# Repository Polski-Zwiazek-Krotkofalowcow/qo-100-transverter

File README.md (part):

# qo-100-transverter

*[Wersja polska / Polish version](README_PL.md)*

## What it's about
- source-available, hardware and software project of a transverter for the [QO-100](https://amsat-uk.org/satellites/geo/eshail-2/) satellite. The outdoor version takes 1.5 days to assemble starting from bare PCB, bag of parts, and patience.
- complete up and down-converter below 199,99 € : [see the BOM](hw-trv/BOM.md)
- in-fab assembly automation in progress

## Equipment and skills required
- knack for SMD soldering with stencil and solder paste
- patience for by-hand component placement
- 10x10 cm heat plate and ability to control the temperature profile
- multimeter
- set of fixed attenuators, a variable one and patch cables
- VNA+SA and a signal generator up to 3GHz minimum
- Pluto-like SDR to receive, measure, and generate signals during tests and adjustments
- RF power meter
- 30V 5A lab power supply with over-current protection
- ST-link programmer
- patience for drilling holes in aluminum enclosure
- patience for tapping 3 mm holes
- RF personal protective equipment rated to attenuate 2.4 GHz frequencies

## Features
- QO-100 narrow-band transponder SSB, CW, and Data operation with an HF-VHF transceiver
- ±0.25 ppm reference oscillator stability
- 6W of 2.4GHz output power
- 10m, 6m, 4m, 2m, 70cm bands supported, 5W input power maximum
- 738MHz filtered, receive output for signal supervision
- 25MHz reference oscillator for LNB: injected into the LNB feeder or the shared output
- PTT-over-coax supported
- splash-proof outdoor version

## Block diagram

## Operation

### Prerequisites

- 28V DC power supply offering 1.1A (31W), or
- 13.8V DC at 3.5A and using the Companion Box for voltage boost
- 60cm dish antenna suggested with 5W ERP according to AMSAT guidelines
- standard universal LNB (13/18V), 500mA fused
- standard PTT ground-to-transmit, or
- PTT-over-coax by transceiver or using the Companion Box to mix PTT and RF
- operation from 13.8V (1.1A) directly is possible with lower output power (2W max). Adequate linearity is not guaranteed.

### Basic procedures

1. Configure IF (Intermediate Frequency) corresponding to your transceiver setup using the three-position slide switch to select one of eight possible IF base frequencies.
2. IF can be updated on-the-fly, the change is indicated by a flashing green LED.
3. Connect DC power and PTT signal.
4. Switch on RX pre-amp in your transceiver.
5. Check the position of the received QO-100 mid beacon, adjust it to fall into the middle of the band using REF ADJ control with a small flat-head screwdriver.
6. Set your transceiver output power to 3–5W and adjust TX ATT control so that your signal is at the mid-beacon level. Lower power with a higher TX ATT setting is advised to minimize heat dissipation inside the transverter.

## Schematics

- [v1.1 schematics (current)](hw-trv/sch_v1.1.pdf) — extra input for 25MHz, idea from Zbig SP3NYF
- [v1.0 schematics](hw-trv/sch_v1.0.pdf) — cheap mini SAW filters + minor enhancements
- [v0.2 schematics](https://github.com/sq5nry/qo-100-transverter/blob/77cc88346982ab3cb6913bec3531f18df363a01a/hw-trv/sch_v0.2.pdf) — release presented at [Ham Radio Friedrichshafen 2026](https://www.hamradio-friedrichshafen.com/trade-show-program/exhibitors/exhibitor?id=107515806) in [PZK](https://www.pzk.org.pl/) (Polish Amateur Radio Union) tent

### PCB manufacturing

The production file set for ordering the v1.1 PCB at [JLCPCB](https://jlcpcb.com/) is available as [qo100_v1.1_jlc_pcb.7z](hw-trv/qo100_v1.1_jlc_pcb.7z).

## Assembly

### Preparation

Gather all parts from the [BOM](hw-trv/BOM.md) and arrange them on your workbench before starting.
Verify IC orientation markings and keep ESD-sensitive parts (ICs, MOSFETs) in their packaging
until placement.

### Solder paste application

Apply solder paste through the PCB stencil. Two paste options have been tested:

- **Sn63Pb37** (183°C eutectic, e.g. Mechanic XG-50) — recommended; standard SnPb profile,
  widely available, easy to work with.
- **Sn42Bi58** (~138°C eutectic, e.g. ChipQuik SMD291 or Mechanic UV50) — low-melting-point
  alternative; useful if heat-sensitive components are a concern, but requires careful handling
  as bismuth alloys are more brittle and less compatible with lead-containing component finishes.

Clamp the stencil firmly over the PCB, apply paste with a squeegee in a single smooth stroke,
and lift the stencil straight up to avoid smearing. Inspect paste deposits under magnification
before placing components.

### Component placement

Place all SMD components onto the paste deposits. Work from smallest to largest — passives first,
then ICs. Pay close attention to pin-1 orientation on all ICs and polarised components.
QFN packages require careful centring over their pads; the paste surface tension will self-align
them slightly during reflow.

### Reflow

Place the populated PCB on the heat plate. Follow a standard **SnPb reflow profile**:

| Zone | Temperature | Duration |
|------|------------|---------|
| Preheat | 100–150°C | ~60 s |
| Soak | 150–180°C | 60–90 s |
| Reflow (above liquidus) | 183–215°C peak | 30–45 s |
| Cooldown | ramp down | natural |

Use hot air to assist reflow around QFN packages and larger thermal-mass parts (PA, DC-DC
converter). Watch for bridging on fine-pitch ICs.
Best option is using a dedicated reflow oven. Otherwise you'll obtain good results with a makeshift greenhouse made from transparent plastics.

### Inspection and rework

After reflow and cooldown, inspect all joints under magnification:

- Remove solder bridges with braid or a fine soldering iron tip.
- Add solder to any under-filled joints, particularly on exposed thermal pads of QFN/PQFN
  packages — use a soldering iron with flux through the heat-via holes on the bottom side.
- The bottom-side thermal vias do not need to be flush; they will be covered by thermal pads
  connecting to the heat spreader or enclosure floor.

### Through-hole parts

Solder the 5W power resistor by hand after SMD reflow. Mount the TCVCXO with polyester
tape and foam fitting as described in the enclosure assembly notes.

### EMI shields

The PCB has footprints for SMD metal EMI shields over sensitive sections. Mounting the shield over the IF Unit is important for stability. Shielding the switched-mode power supply section and TCXO is recommended but not critical.
I haven't noticed any adverse effects with no EMI shields at all, especially with metal enclosure and EMI absorber mounted.

### EMI absorber

Most of enclosure types require absorption foams in PA area to help suppress self-oscillations and minimize parasitic coupling between stages. The amplifier may start self-oscillations at a frequency between 2.2-2.5GHz with full power without the absorber. \
See gallery section for a poor's-man approach.

### PCB cleaning

Wash the assembled PCB thoroughly with isopropanol to remove all flux residues before
proceeding. Flux contamination on the board surface can significantly affect 2.4GHz circuit
behaviour — altering tuning, increasing losses, and making RF adjustments unreliable.
Allow the board to dry completely before applying power.

### Power-up and initial checks

Connect power and PTT cables. Supply 28V with the current limit set to 50mA. Measure the
following test points and verify voltages before proceeding:

1. Check 13V and 5V test points first.
2. If those are correct, verify: 3V (analog), 3V (digital), 3.3V (reference oscillator),
   3V (MCU), 9V, and 1.8V.

If any rail is missing or out of range, do not proceed — investigate before applying full power.

### Firmware

Flash the firmware using **STM32CubeProgrammer** via the ST-LINK interface and the SWD ISP
header. A firmware release binary is provided; to build from source use **STM32CubeIDE**.

After programming, the **PLL LOCK** indicator should illuminate. If it does not, check the
25MHz reference oscillator signal.

### PA bias adjustment

Set the quiescent drain current (Idq) for the 2.4GHz PA stages:

- 1st stage: **15mA**
- 2nd stage: **75mA**

Before adjusting, raise the lab supply's overload protection (current limit) to about
**250mA** so it does not trip during bias trimming.

To measure Idq, cut the respective drain supply PCB trace and insert an ammeter in series or just calculate current delta on the lab supply.
Adjust the bias trimmer for each stage until the target Idq is reached, then bridge the cut
with solder.
Adjust the position of C87 in the PA output circuit for highest stage gain.

### PA gain and output matching

Measure the PA gain and adjust the position of C88 to obtain **28–30dB** gain — slide C88 along the output line toward the thicker section. If that alone does not maximise gain, add 0.8pF in parallel with C88. Do not mount the low-pass filter (LPF) elements yet — bridge the LPF inductor footprint with a strip of
copper foil instead, so the PA output can be measured without the potentially mismatched filter.

Once the gain is set, mount the LPF inductor and adjust it for a maximum insertion loss of
**1dB at 2.4GHz**.

Set the overload (overcurrent) protection threshold to **1.1A**.

Connect an RF power meter to the 2.4GHz TX output socket and adjust the TX path for **6W**
output across your expected input power range (1–5W).

> **⚠️ Warning:** do not increase input power in an attempt to reach 6W until PA gain is at least 28dB. PA chip will overheat and operate non-linearly. I bricked one PA after overloading its input with just 17dBm.

> **⚠️ Warning:** do not drive the PA past **9..12W** output — exceeding this limit pushes the
> stage into non-linear operation, causing spectral splatter and interference to other users.

> **⚠️ Note:** the PA chip tolerates antenna mismatch well — SWR up to 10:1 on the 2.4GHz
> TX port will not damage it. However, operating with no load connected may cause
> self-oscillation in the 2.2–2.5GHz range; the on-board 1.5A resettable fuse will limit
> the resulting current in that event.

## Circuit description

### Transmit path

The transceiver signal (up to 5W / +37dBm) passes through a variable 35–42dB attenuator,
reducing it to approximately −8dBm at the mixer input. A diode protection limiter with a
clipping level starting softly at +4dBm guards the mixer — this is to limit damage in case you connect 100W for a longer time. Note that sustained high-power overshoots may still damage the PA by exceeding its maximum input level even if the mixer itself survives. \
The signal enters a balanced Gilbert-cell mixer (RFFC2071). The mixer's wideband 4:1 output transformer provides differential symmetry that helps cancel LO leakage, minimising it before the signal
 reaches the downstream filter. Although slightly more expensive than a narrowband balun
chip, the wideband transformer's superior symmetry keeps LO leakage below −50dBc relative
to the upper sideband with only two mini SAW filters — most critically on the 29MHz band, where
LO leakage lands closest to occupied spectrum. The TX mixer on 10m is intentionally operated at a reduced  current, which directly decreases LO leakage at its output. \
The output is filtered by two 2.4GHz bandpass filters to further suppress residual LO leakage as well as the image. The driver stage amplifies the signal to +12dBm, followed by a 29dB LDMOS power amplifier — whose input is matched to 50Ω using a short high-impedance transmission line — and a low-pass filter, delivering +38dBm (6W) to
the TX output socket. \
1dB and 3dB fixed attenuation pads improve impedance matching, distribute gain, and improve amplifier stability.\
Image attenuation is better than 60dB on 10m.
Total conversion gain is 2–9dB; about 0.8–4W from the transceiver will produce 6W output.

### Receive path

Both the LNB supply voltage and the 25MHz reference signal (along with its harmonics up to 125MHz) are injected via a bias-T, which must provide sufficient RF isolation across the full 25–738MHz range where these signals share the same junction. The reference signal is low-pass filtered to 125MHz before injection. \
The received 738MHz IF from the LNB passes through a high-pass filter (so as not to hammer the input SAW filters with the reference oscillator) and two cascaded SAW filters centred around 738MHz. Then follows optional splitter to tap IF to the external RX AUX socket. Release v0.2 uses resistive splitter but it's advised to use minimum-loss option as in v0.3-sh. If you don't need the RX AUX output, do not mount the splitter parts.\
From the mixer output the signal passes through a PIN diode switch to the shared TRX socket. The switch's bias-T is built from three inductors in series, chosen to present at least 1kΩ of reactance at
every supported IF band. \
The input attenuator is always present on the RX path — enable the RX preamplifier in your
transceiver to compensate. The receive path does not add amplification (to keep the cost low) and relies on typical LNB signal levels so as not to degrade the SNR with noise from the RX chain. \
On 70cm IF the strongest signals come at S9 level with RX preamp on, mid-beacon is S7.

### Control

The STM32L0 microcontroller configures the RFFC2071 PLL for the RX and TX frequencies corresponding to the IF band selected by the DIP switch. In addition, mixer bias currents ate also configurd per band. On PTT transitions, the logic switches between the TX and RX PLL register banks in the RFFC2071. The PTT signal is a logical OR from the physical PTT line and the coax (PTT-over-coax).

### Indicators

The blue LED indicates that the PLL synthesizer is locked — the MCU has configured the PLL, the 25MHz reference is running, and the LO frequency is being generated. Mixer bias currents are configured according to IF band.

The green LED blinks in RX mode and is lit continuously in TX mode. On startup and on IF band change, it blinks once per IF position number (1–8).

## Jumper configuration

### Jumper reference

| Jumper | Name | Default | Function |
|--------|------|---------|----------|
| JP1 | AUX SEL | Reference | Selects what the RX/REF (AUX) socket outputs: **Reference** (25MHz) or **RX** (738MHz) |
| JP2 | RX SPLIT | no-split | Part of RX split — change together with JP4. Change position only if you want RX in AUX socket. |
| JP4 | RX SPLIT | no-split | Part of RX split — change together with JP2. Change position only if you want RX in AUX socket. |
| JP5 | OVEN | disconnected | Reserved for OCXO option; disabled in v0.2 |
| JP6 | REF ROUTE | AUX path | Routes the 25MHz reference toward the AUX socket (default) or toward the LNB feeder (also check JP7) |
| JP7 | REF TO LNB | open | Solder to mix the 25MHz reference signal into the LNB feeder coax. This jumper enhances signal integrity when the REF signal isn't routed to the LNB feeder. "Open" when you don't want to mix the REF with the LNB feeder, "Connected" to inject the REF into the LNB feeder. |
| JP8 | REF SEL | ext ref | Selects the source of the 25MHz reference signal: the **internal TCXO** or an **external reference** fed to the REF_IN socket. |
| JP9 | REF_IN TERM | open | Connects the internal 50Ω termination to REF_IN. "Open" leaves REF_IN unterminated, "Connected" (solder) terminates it with 50Ω. |

### Typical usage scenarios

**1. RX/REF (AUX) socket outputs 25MHz reference** *(default — no changes needed)*

Use this to supply 25MHz reference to an external device via the AUX socket.

| JP1 | JP2 | JP4 | JP6 | JP7 |
|-----|-----|-----|-----|-----|
| default (Reference) | default | default | default (AUX path) | open |

---

**2. 25MHz reference injected into LNB feeder cable**

Use this when the LNB is fed its reference via the coax (no separate reference cable needed).

| JP1 | JP2 | JP4 | JP6 | JP7 |
|-----|-----|-----|-----|-----|
| default | default | default | **change (LNB path)** | **solder** |

---

**3. RX signal (738MHz) on AUX socket**

Use this to route the received downconverted signal to an external SDR or receiver via the AUX socket.

| JP1 | JP2 | JP4 | JP6 | JP7 |
|-----|-----|-----|-----|-----|
| **change (RX)** | **change** | **change** | default | open |

---

**4. Reference injected into LNB feeder + RX signal on AUX socket**

Combines use cases 2 and 3: LNB gets its reference via coax, AUX socket carries the RX signal.

| JP1 | JP2 | JP4 | JP6 | JP7 |
|-----|-----|-----|-----|-----|
| **change (RX)** | **change** | **change** | **change (LNB path)** | **solder** |

---

## Gallery

<table>
<tr>
<td align="center"><br><em>Click the image to watch the video.</em></td>
<td align="center"><br><em>Infrared video of the PCB during PA test — passive cooling via aluminum enclosure. Click to watch.</em></td>
</tr>
</table>

<table>
<tr>
<td align="center"><br><em>Output power — click to watch. 40dB/50W att. + 20dB SMA att (39.5+19,5=59dB at 2.4GHz)</em></td>
<td align="center"><br><em>Power measurements — click to watch. Heat-pipe directly at PA.</em></td>
</tr>
</table>

### v1.0 bare board

<table>
<tr>
<td></td>
<td></td>
</tr>
</table>

### Finished units

<table>
<tr>
<td><br><em>cabinet, outdoor classic, outdoor mini, bare bone</em></td>
<td><br><em>cabinet version</em></td>
</tr>
<tr>
<td><br><em>outdoor mini</em></td>
<td><br><em>Companion Box</em></td>
</tr>
<tr>
<td><br><em>cabinet version, back plate</em></td>
<td><br><em>cabinet mini</em></td>
</tr>
</table>

### Enclosure internals

<table>
<tr>
<td><br><em>cabinet version</em></td>
<td><br><em>outdoor classic</em></td>
</tr>
<tr>
<td><br><em>cabinet version</em></td>
<td><br><em>cabinet version</em></td>
</tr>
<tr>
<td><br><em>Companion Box proof-of-concept</em></td>
<td><br><em>outdoor mini</em></td>
</tr>
</table>

### PCB assembly

<table>
<tr>
<td></td>
<td></td>
<td></td>
</tr>
<tr>
<td></td>
<td></td>
<td></td>
</tr>
<tr>
<td></td>
<td></td>
<td></td>
</tr>
<tr>
<td></td>
<td></td>
<td></td>
</tr>
<tr>
<td></td>
<td></td>
<td></td>
</tr>
</table>

### PCB details

<table>
<tr>
<td><br><em>2.8GHz low-pass filter</em></td>
<td></td>
</tr>
<tr>
<td></td>
<td></td>
</tr>
<tr>
<td><br><em>replacing IF chip</em></td>
<td></td>
</tr>
</table>

### EMI absorbers

<table>
<tr>
<td></td>
<td></td>
</tr>
<tr>
<td></td>
<td></td>
</tr>
</table>

### Development and testing

<table>
<tr>
<td></td>
<td></td>
</tr>
<tr>
<td></td>
<td></td>
</tr>
<tr>
<td></td>
<td></td>
</tr>
<tr>
<td></td>
<td></td>
</tr>
<tr>
<td></td>
<td><br><em>a cheap C88 (ordinary ceramic instead of ATC porcelain one)</em></td>
</tr>
</table>

### Measurements

<table>
<tr>
<td></td>
<td></td>
</tr>
</table>

## Measurements - TX & RX paths

### TX mixer-to-driver-out, LDMOS gain

<table>
<tr>
<td></td>
<td></td>
</tr>
</table>

### LO, upper sideband, image, and 2nd harmonic levels

<table>
<tr>
<td></td>
<td></td>
</tr>
<tr>
<td></td>
<td></td>
</tr>
</table>

### TRX port

<table>
<tr>
<td align="center"><br><em>TRX port on TX, s11</em></td>
<td align="center"><br><em>TRX port on RX, s11</em></td>
</tr>
</table>

> **⚠️ Note:** TX SWR on 23cm is high. Only RX has been tested and confirmed on this band. Proper TX 23cm testing is in progress — it may work with ALC-limited power from your transceiver.

### RF filtering

*two 739MHz filters cascaded incl. balun loss*

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
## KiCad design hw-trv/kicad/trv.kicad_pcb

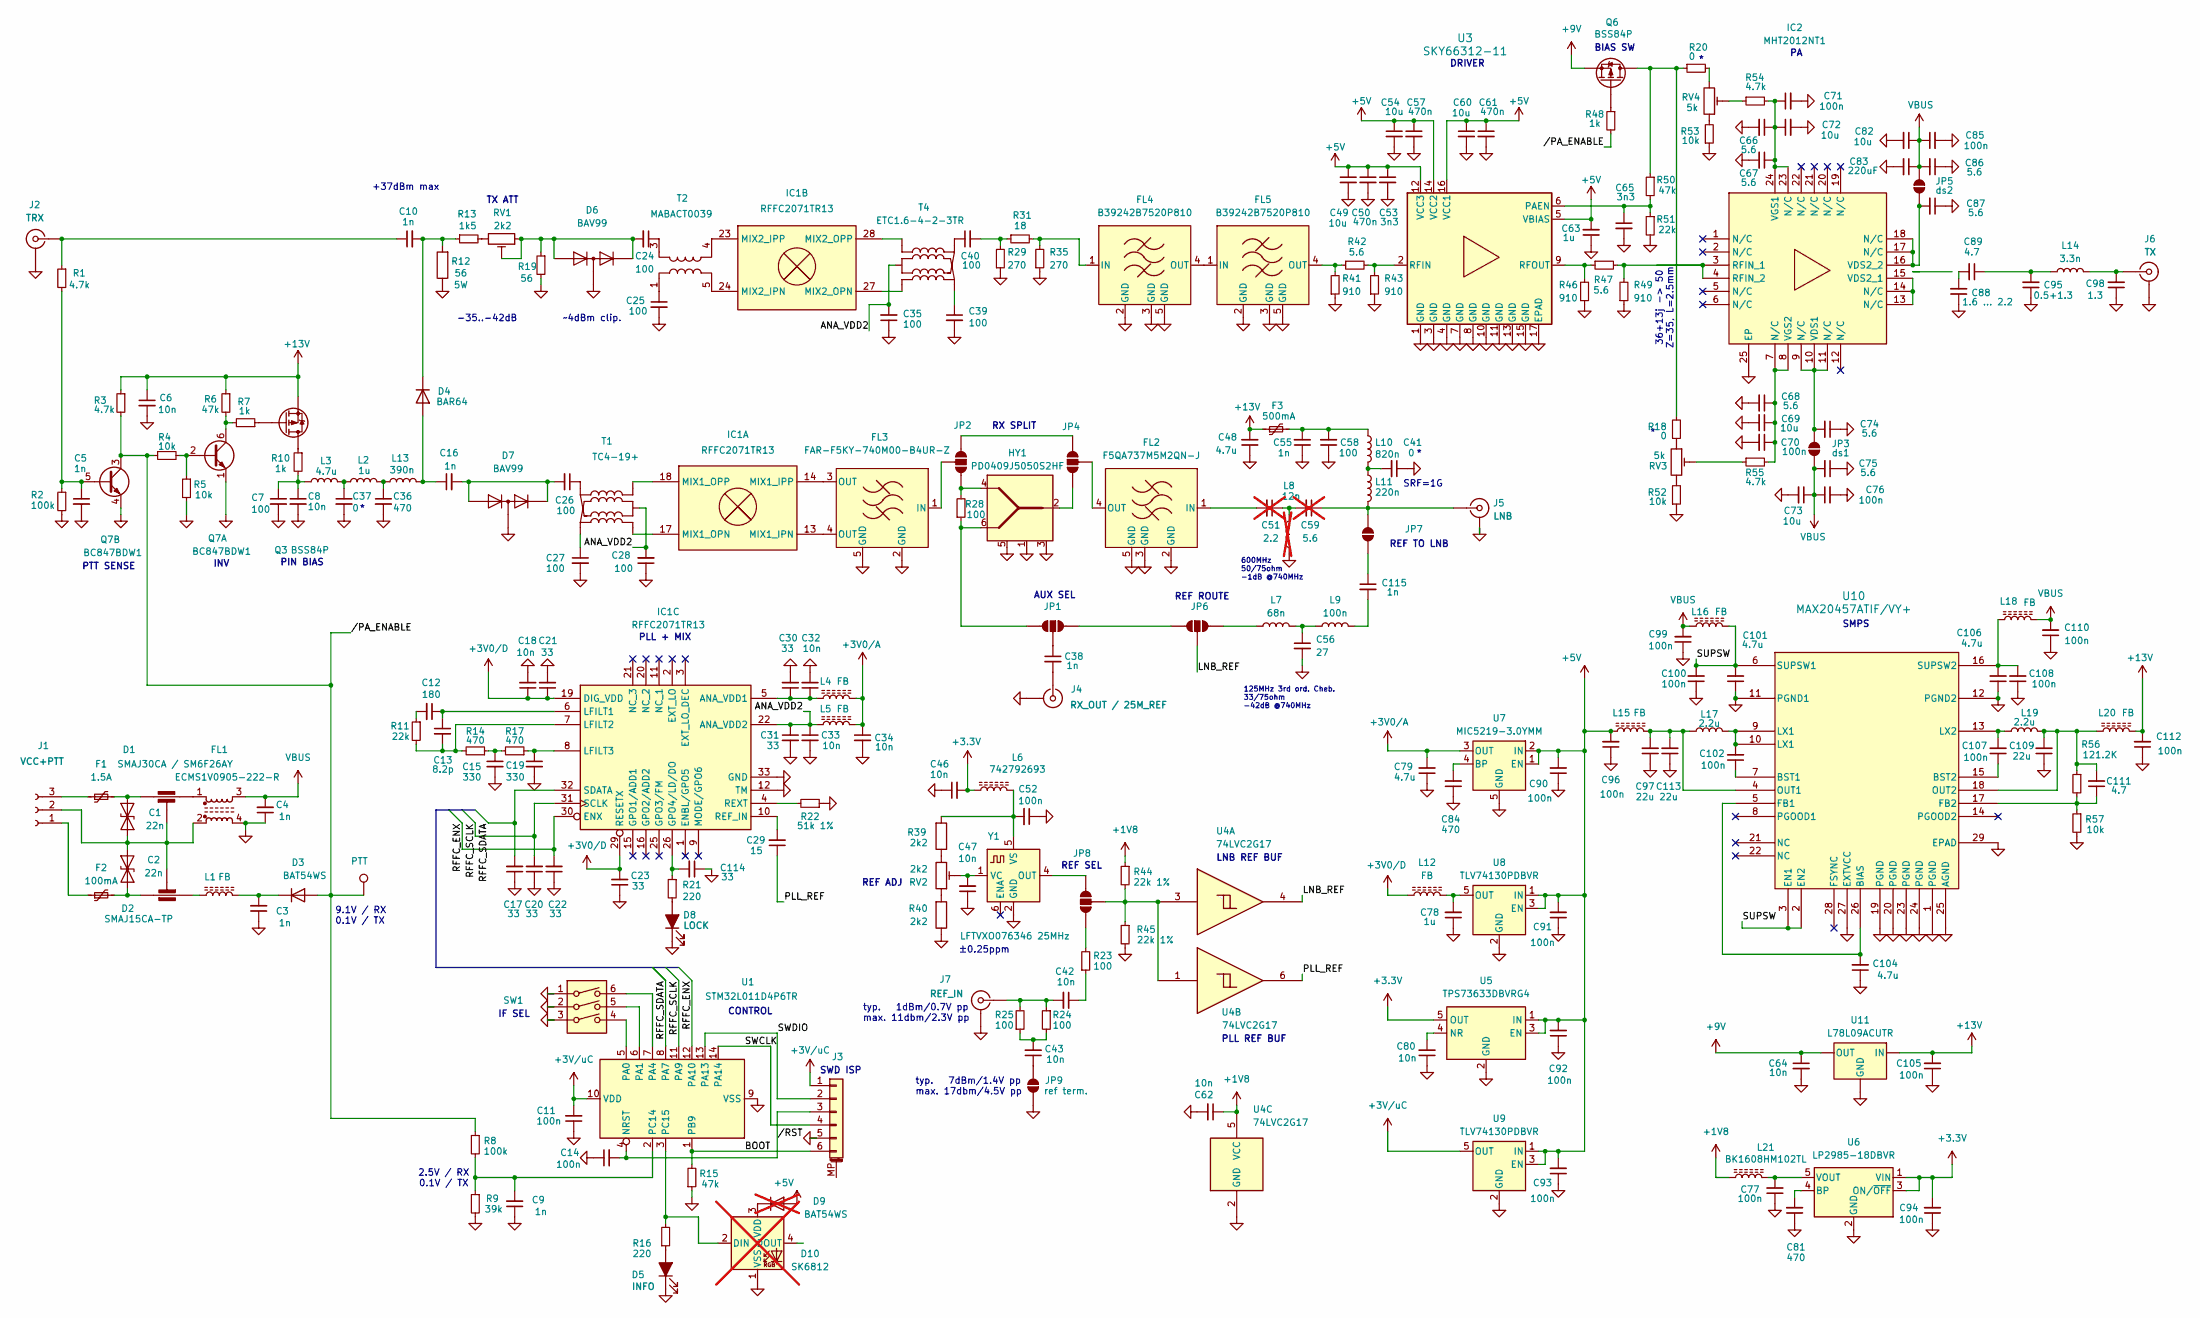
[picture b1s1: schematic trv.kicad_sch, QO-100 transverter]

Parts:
C1: 22n; Filter_Mini-Circuits_FV1206; Voltage 100V
C2: 22n; Filter_Mini-Circuits_FV1206; Voltage 50V
C3, C4, C5, C9, C16, C38, C55, C115: 1n; C_0603_1608Metric_Pad1.08x0.95mm_HandSolder; Voltage 35V
C6, C8, C18, C32, C33, C34, C46, C47, C62, C64, C80: 10n; C_0603_1608Metric_Pad1.08x0.95mm_HandSolder; Voltage 16V
C7, C58: 100; C_0603_1608Metric_Pad1.08x0.95mm_HandSolder; Voltage 35V
C10: 1n; C_0603_1608Metric_Pad1.08x0.95mm_HandSolder; Voltage 100V
C11, C14, C52, C77, C90, C91, C92, C93, C94: 100n; C_0603_1608Metric_Pad1.08x0.95mm_HandSolder; Voltage 16V
C12: 180; C_0603_1608Metric_Pad1.08x0.95mm_HandSolder; Voltage 16V
C13: 8.2p; C_0603_1608Metric_Pad1.08x0.95mm_HandSolder; Voltage 16V
C15, C19: 330; C_0603_1608Metric_Pad1.08x0.95mm_HandSolder; Voltage 16V
C17, C20, C21, C22, C23, C30, C31, C114: 33; C_0603_1608Metric_Pad1.08x0.95mm_HandSolder; Voltage 16V
C24, C25, C26, C27, C28, C35, C39, C40: 100; C_0603_1608Metric_Pad1.08x0.95mm_HandSolder; Voltage 16V
C29: 15; C_0603_1608Metric_Pad1.08x0.95mm_HandSolder; Voltage 16V
C36: 470; C_0603_1608Metric_Pad1.08x0.95mm_HandSolder; Voltage 35V
C37, C41: 0; C_0603_1608Metric_Pad1.08x0.95mm_HandSolder; Voltage 35V
C42, C43: 10n; C_0603_1608Metric_Pad1.08x0.95mm_HandSolder; Voltage 35V
C48: 4.7u; C_1206_3216Metric; Voltage 25V
C49, C54, C60: 10u; C_1210_3225Metric; Voltage 16V
C50, C57, C61: 470n; C_0603_1608Metric_Pad1.08x0.95mm_HandSolder; Voltage 16V
C51: 2.2; C_0603_1608Metric_Pad1.08x0.95mm_HandSolder; Voltage 35V; not fitted
C53, C65: 3n3; C_0603_1608Metric_Pad1.08x0.95mm_HandSolder; Voltage 16V
C56: 27; C_0603_1608Metric_Pad1.08x0.95mm_HandSolder; Voltage 35V
C59: 5.6; C_0603_1608Metric_Pad1.08x0.95mm_HandSolder; Voltage 35V; not fitted
C63, C78: 1u; C_0603_1608Metric_Pad1.08x0.95mm_HandSolder; Voltage 16V
C66, C67, C68, C74, C75, C86, C87: 5.6; L_0805_2012Metric; Voltage 250V
C69, C72, C73, C82: 10u; C_1210_3225Metric; Voltage 50V
C70, C71, C76, C85: 100n; C_1210_3225Metric; Voltage 100V
C79: 4.7u; CP_EIA-3528-21_Kemet-B_HandSolder; Voltage 10V
C81, C84: 470; C_0603_1608Metric_Pad1.08x0.95mm_HandSolder; Voltage 16V
C83: 220uF; CP_Elec_6.3x5.8; Voltage 35V
C88: 1.6 ... 2.2; C_0805_2012Metric; Voltage 250V
C89: 4.7; C_0805_2012Metric_Pad1.18x1.45mm_HandSolder; Voltage 250V
C95: 0.5+1.3; C_0805_2012Metric; Voltage 250V
C96, C99, C100, C108, C110: 100n; C_1206_3216Metric; Voltage 35V
C97, C113: 22u; C_1206_3216Metric_Pad1.33x1.80mm_HandSolder; Voltage 10V
C98: 1.3; C_0805_2012Metric; Voltage 250V
C101, C106: 4.7u; C_1206_3216Metric; Voltage 35V
C102, C107: 100n; C_0603_1608Metric; Voltage 50V
C104: 4.7u; C_0603_1608Metric_Pad1.08x0.95mm_HandSolder; Voltage 16V
C105: 100n; C_0603_1608Metric_Pad1.08x0.95mm_HandSolder; Voltage 50V
C109: 22u; C_1206_3216Metric_Pad1.33x1.80mm_HandSolder; Voltage 25V
C111: 4.7; C_0603_1608Metric_Pad1.08x0.95mm_HandSolder; Voltage 35V
C112: 100n; C_1206_3216Metric_Pad1.33x1.80mm_HandSolder; Voltage 35V
D1: SMAJ30CA / SM6F26AY; D_SMA
D2: SMAJ15CA-TP; D_SMA
D3: BAT54WS; D_SOD-323F
D4: BAR64; D_SOD-523
D5: INFO; LED_0805_2012Metric_Pad1.15x1.40mm_HandSolder
D6, D7: BAV99; SOT-23-3
D8: LOCK; LED_0805_2012Metric_Pad1.15x1.40mm_HandSolder
D9: BAT54WS; D_SOD-323F; not fitted
D10: SK6812; LED_SK6812_PLCC4_5.0x5.0mm_P3.2mm; not fitted
F1: 1.5A; Fuse_2920_7451Metric_Pad2.10x5.45mm_HandSolder
F2: 100mA; Fuse_1210_3225Metric_Pad1.42x2.65mm_HandSolder
F3: 500mA; Fuse_1206_3216Metric_Pad1.42x1.75mm_HandSolder
FL1: ECMS1V0905-222-R; L_CommonModeChoke_TDK_ACM7060
FL2: F5QA737M5M2QN-J; SMD5_SAW-B7520_QUA
FL3: FAR-F5KY-740M00-B4UR-Z; FAR-F5KY
FL4, FL5: B39242B7520P810; SMD5_SAW-B7520_QUA
HY1: PD0409J5050S2HF; Manufacturer_Part_Number PD0409J5050S2HF; Mouser Part Number 620-PD0409J5050S2HF
IC1: RFFC2071TR13; Manufacturer_Part_Number RFFC2071TR13; Mouser Part Number 772-RFFC2071
IC2: MHT2012NT1; Mouser Part Number 771-MHT2012NT1
J1: VCC+PTT; 874370363
J2: TRX; SMA_Amphenol_132289_EdgeMount
J3: SWD ISP; PinHeader_2x03_P2.54mm_Vertical_SMD
J4: RX_OUT / 25M_REF; SMA_Amphenol_132289_EdgeMount
J5: LNB; 222131
J6: TX; SMA_Wurth_60312102114405_Vertical
J7: REF_IN; SMA_Amphenol_132289_EdgeMount
JP1, JP2, JP4, JP6, JP8: SolderJumper_3_Open; SolderJumper-3_P1.3mm_Bridged12_RoundedPad1.0x1.5mm_NumberL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
JP3: ds1
JP5: ds2
JP7: SolderJumper_2_Open; SolderJumper-2_P1.3mm_Open_RoundedPad1.0x1.5mm
JP9: ref term.; SolderJumper-2_P1.3mm_Open_RoundedPad1.0x1.5mm
L1, L15, L16, L18, L20: FB; L_1812_4532Metric_Pad1.30x3.40mm_HandSolder
L2: 1u; L_1008_2520Metric_Pad1.43x2.20mm_HandSolder
L3: 4.7u; L_0805_2012Metric_Pad1.05x1.20mm_HandSolder
L4, L5, L12: FB; L_0603_1608Metric_Pad1.05x0.95mm_HandSolder
L6: 742792693; L_0603_1608Metric_Pad1.05x0.95mm_HandSolder
L7: 68n; L_0805_2012Metric_Pad1.05x1.20mm_HandSolder
L8: 12n; L_0603_1608Metric_Pad1.05x0.95mm_HandSolder; not fitted
L9: 100n; L_0805_2012Metric_Pad1.05x1.20mm_HandSolder
L10: 820n; L_1008_2520Metric_Pad1.43x2.20mm_HandSolder
L11: 220n; L_0603_1608Metric_Pad1.05x0.95mm_HandSolder
L13: 390n; L_Cenker_CKCS252012
L14: 3.3n; L_0805_2012Metric_Pad1.05x1.20mm_HandSolder
L17, L19: 2.2u; INDPM7168X300N
L21: BK1608HM102TL; L_0603_1608Metric_Pad1.05x0.95mm_HandSolder
PTT1: PTT; TestPoint_Pad_D1.5mm
Q3, Q6: BSS84P; SOT-23
Q7: BC847BDW1; SOT-363_SC-70-6
R1, R3, R54, R55: 4.7k; R_0603_1608Metric_Pad0.98x0.95mm_HandSolder
R2, R8: 100k; R_0603_1608Metric_Pad0.98x0.95mm_HandSolder
R4, R5, R52, R53, R57: 10k; R_0603_1608Metric_Pad0.98x0.95mm_HandSolder
R6, R15, R50: 47k; R_0603_1608Metric_Pad0.98x0.95mm_HandSolder
R7, R10, R48: 1k; R_0603_1608Metric_Pad0.98x0.95mm_HandSolder
R9: 39k; R_0603_1608Metric_Pad0.98x0.95mm_HandSolder
R11, R51: 22k; R_0603_1608Metric_Pad0.98x0.95mm_HandSolder
R12: 56; RES_3550_TEC
R13: 1k5; R_0603_1608Metric_Pad0.98x0.95mm_HandSolder
R14, R17: 470; R_0603_1608Metric_Pad0.98x0.95mm_HandSolder
R16, R21: 220; R_0603_1608Metric_Pad0.98x0.95mm_HandSolder
R18, R20: 0; R_0603_1608Metric_Pad0.98x0.95mm_HandSolder
R19: 56; R_0603_1608Metric_Pad0.98x0.95mm_HandSolder
R22: 51k 1%; R_0603_1608Metric_Pad0.98x0.95mm_HandSolder
R23, R24, R25, R28: 100; R_0603_1608Metric_Pad0.98x0.95mm_HandSolder
R29, R35: 270; R_0603_1608Metric_Pad0.98x0.95mm_HandSolder
R31: 18; R_0603_1608Metric_Pad0.98x0.95mm_HandSolder
R39, R40: 2k2; R_0603_1608Metric_Pad0.98x0.95mm_HandSolder
R41, R43, R46, R49: 910; R_0603_1608Metric_Pad0.98x0.95mm_HandSolder
R42, R47: 5.6; R_0603_1608Metric_Pad0.98x0.95mm_HandSolder
R44, R45: 22k 1%; R_0805_2012Metric_Pad1.20x1.40mm_HandSolder
R56: 121.2K; R_0603_1608Metric_Pad0.98x0.95mm_HandSolder
RV1: 2k2; Potentiometer_Bourns_TC33X_Vertical
RV2: 2k2; Potentiometer_Bourns_3314J_Vertical
RV3, RV4: 5k; Potentiometer_Bourns_TC33X_Vertical
SW1: SW_DIP_x03; SW_DIP_SPSTx03_Slide_KingTek_DSHP03TJ_W5.25mm_P1.27mm_JPin
T1: TC4-19+; ETC1.6-4-2-3TR_MCM
T2: MABACT0039; MABACT0039_MCM
T4: ETC1.6-4-2-3TR; ETC1.6-4-2-3TR_MCM
U1: STM32L011D4P6TR; TSSOP-14_4.4x5mm_P0.65mm
U3: SKY66312-11; QFN16_5X5_SKY
U4: 74LVC2G17; Vishay_PowerPAK_SC70-6L_Dual
U5: TPS73633DBVRG4; SOT-23-5
U6: LP2985-18DBVR; SOT-23-5
U7: MIC5219-3.0YMM; MSOP-8_3x3mm_P0.65mm
U8, U9: TLV74130PDBVR; SOT-23-5
U10: MAX20457ATIF/VY+; 21-100130_MXM
U11: L78L09ACUTR; SOT-89-3
Y1: LFTVXO076346 25MHz; LFTVXO076346REEL_IQD-M

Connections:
+1V8: C62.1, L21.1, R44.1, U4.5 (VCC)
+3.3V: C46.2, C94.2, L6.1, U5.5 (OUT), U6.1 (VIN), U6.3 (ON/~OFF)
+3V0/A: C34.1, C79.2, L4.2, L5.2, U7.3 (OUT); also elsewhere on the board
+3V0/D: C18.1, C21.1, C23.2, IC1.19 (DIG_VDD), IC1.29 (RESETX), L12.1; also elsewhere on the board
+3V/uC: C11.2, J3.1, U1.10 (VDD), U9.5 (OUT)
+5V: C49.1, C50.1, C53.1, C54.1, C57.1, C60.1, C61.1, C63.2, C90.2, C91.2, C92.2, C93.2, C96.2, D9.2 (A), L15.1, U3.5 (VBIAS), U3.12 (VCC3), U3.14 (VCC2), U3.16 (VCC1), U5.1 (IN), U5.3 (EN), U7.1 (EN), U7.2 (IN), U8.1 (IN), U8.3 (EN), U9.1 (IN), U9.3 (EN); also elsewhere on the board
+9V: C64.1, Q6.2 (S), U11.1 (OUT); also elsewhere on the board
+13V: C6.1, C48.2, C105.2, C112.2, F3.1, L20.2, Q3.2 (S), R3.1, R6.1, U11.3 (IN); also elsewhere on the board
/ANA_VDD2: C28.2, C31.1, C33.1, C35.2, IC1.22 (ANA_VDD2), L5.1, T1.2, T4.2
/BOOT: J3.6, R15.2, U1.1 (PB9)
/LNB_REF: JP6.2 (C), U4.4
/PLL_REF: C29.1, U4.6
/RFFC_ENX: C22.2, IC1.30 (ENX), U1.12 (PA10)
/RFFC_SCLK: C20.2, IC1.31 (SCLK), U1.11 (PA9)
/RFFC_SDATA: C17.2, IC1.32 (SDATA), U1.8 (PA7)
/SUPSW: C100.2, C101.2, L16.2, U10.2 (EN2), U10.3 (EN1), U10.6 (SUPSW1)
/SWCLK: J3.4, U1.14 (PA14)
/SWDIO: J3.2, U1.13 (PA13)
//PA_ENABLE: D3.2 (A), PTT1.1, Q7.3 (C2), R3.2, R4.1, R8.1, R48.2; also elsewhere on the board
//RST: C14.2, J3.3, U1.4 (NRST)
GND: C3.1, C4.1, C5.2, C6.2, C7.2, C8.2, C9.1, C11.1, C14.1, C15.2, C17.1, C18.2, C19.2, C20.1, C21.2, C22.1, C23.1, C25.2, C27.2, C28.1, C30.2, C31.2, C32.2, C33.2, C34.2, C35.1, C36.2, C37.2, C39.2, C41.1, C46.1, C47.1, C48.1, C49.2, C50.2, C52.1, C53.2, C54.2, C55.1, C56.2, C57.2, C58.1, C60.2, C61.2, C62.2, C63.1, C64.2, C65.2, C66.2, C67.2, C68.2, C69.2, C70.2, C71.2, C72.2, C73.2, C74.1, C75.1, C76.2, C77.1, C78.1, C79.1, C80.1, C81.1, C82.2, C83.2, C84.1, C85.2, C86.1, C87.1, C88.1, C90.1, C91.1, C92.1, C93.1, C94.1, C95.1, C96.1, C97.1, C98.1, C99.1, C100.1, C101.1, C104.1, C105.1, C106.1, C108.1, C109.1, C110.1, C112.1, C113.1, C114.1, D5.1 (K), D6.3 (K), D7.3 (K), D8.1 (K), D10.1 (VSS), FL1.4, FL2.2 (GND), FL2.3 (GND), FL2.5 (GND), FL3.2 (GND), FL3.5 (GND), FL4.2 (GND), FL4.3 (GND), FL4.5 (GND), FL5.2 (GND), FL5.3 (GND), FL5.5 (GND), HY1.1, HY1.3, HY1.5, IC1.12 (TM), IC1.33 (GND), IC2.25 (EP), J2.2 (Ext), J3.5, J4.2 (Ext), J5.2 (Ext), J6.2 (Ext), J7.2 (Ext), JP9.2 (B), L8.1, Q7.1 (E1), Q7.4 (E2), R2.2, R5.2, R9.2, R12.1, R15.1, R19.2, R22.1, R29.1, R35.1, R40.1, R41.1, R43.1, R45.2, R46.1, R49.1, R51.2, R52.1, R53.1, R57.2, SW1.1, SW1.2, SW1.3, U1.9 (VSS), U3.1 (GND), U3.3 (GND), U3.4 (GND), U3.7 (GND), U3.8 (GND), U3.10 (GND), U3.11 (GND), U3.13 (GND), U3.15 (GND), U3.17 (EPAD), U4.2 (GND), U5.2 (GND), U6.2 (GND), U7.5 (GND), U7.6 (GND), U7.7 (GND), U7.8 (GND), U8.2 (GND), U9.2 (GND), U10.1 (PGND), U10.11 (PGND1), U10.12 (PGND2), U10.19 (PGND), U10.20 (PGND), U10.23 (PGND), U10.24 (PGND), U10.25 (AGND), U10.27 (EXTVCC), U10.29 (EPAD), U11.2 (GND), Y1.2 (GND)
unnamed: C1.3, FL1.1
unnamed: C2.1, L1.1
unnamed: C7.1, C8.1, L3.2, R10.2
unnamed: C12.2, R11.1
unnamed: C15.1, R14.1, R17.2
unnamed: C24.1, T2.3
unnamed: C25.1, T2.1
unnamed: C26.1, T1.5
unnamed: C27.1, T1.4
unnamed: C36.1, L2.2, L13.1
unnamed: C37.1, L2.1, L3.1
unnamed: C39.1, T4.4
unnamed: C40.1, T4.5
unnamed: C40.2, R29.2, R31.1
unnamed: C41.2, L10.2, L11.1
unnamed: C42.1, R23.1
unnamed: C43.2, R24.2, R25.1
unnamed: C51.1, C59.2, L8.2
unnamed: C55.2, C58.2, F3.2, L10.1
unnamed: C56.1, L7.2, L9.1
unnamed: C88.2, C89.2
unnamed: C89.1, C95.2, L14.1
unnamed: C102.2, L17.2, U10.9 (LX1), U10.10 (LX1)
unnamed: C115.2, L9.2
unnamed: C1.2, C2.2, D1.1 (A1), D2.2 (A2), FL1.2, J1.2
unnamed: C1.1, D1.2 (A2), F1.2
unnamed: C2.3, D2.1 (A1), F2.2
unnamed: C3.2, D3.1 (K), L1.2
unnamed: C16.1, D4.2 (A), L13.2
unnamed: C10.2, D4.1 (K), R12.2, R13.1
unnamed: D5.2 (A), R16.1
unnamed: C24.2, D6.1 (K), D6.2 (A), R19.1, RV1.1, RV1.2
unnamed: C16.2, C26.2, D7.1 (K), D7.2 (A)
unnamed: D8.2 (A), R21.2
unnamed: D9.1 (K), D10.3 (VDD)
unnamed: C51.2, FL2.1 (IN)
unnamed: FL2.4 (OUT), JP4.2 (C)
unnamed: FL3.1 (IN), JP2.2 (C)
unnamed: FL4.1 (IN), R31.2, R35.2
unnamed: FL4.4 (OUT), FL5.1 (IN)
unnamed: FL5.4 (OUT), R41.2, R42.1
unnamed: FL3.4 (OUT), IC1.13 (MIX1_IPN)
unnamed: FL3.3 (OUT), IC1.14 (MIX1_IPP)
unnamed: IC1.17 (MIX1_OPN), T1.3
unnamed: IC1.18 (MIX1_OPP), T1.1
unnamed: IC1.24 (MIX2_IPN), T2.5
unnamed: IC1.23 (MIX2_IPP), T2.4
unnamed: IC1.27 (MIX2_OPN), T4.3
unnamed: IC1.28 (MIX2_OPP), T4.1
unnamed: C30.1, C32.1, IC1.5 (ANA_VDD1), L4.1
unnamed: C114.2, IC1.26 (GPO4/LD/DO), R21.1
unnamed: C12.1, C13.1, IC1.6 (LFILT1)
unnamed: C13.2, IC1.7 (LFILT2), R11.2, R14.2
unnamed: C19.1, IC1.8 (LFILT3), R17.1
unnamed: C29.2, IC1.10 (REF_IN)
unnamed: IC1.4 (REXT), R22.2
unnamed: IC2.3 (RFIN_1), IC2.4 (RFIN_2), R47.2, R49.2
unnamed: C74.2, IC2.9 (N/C), IC2.10 (VDS1), IC2.11 (N/C), JP3.2 (B)
unnamed: IC2.13 (N/C), IC2.14 (N/C), IC2.15 (VDS2_1)
unnamed: C87.2, IC2.16 (VDS2_2), IC2.17 (N/C), IC2.18 (N/C), JP5.1 (A)
unnamed: C66.1, C67.1, C71.1, C72.1, IC2.23 (N/C), IC2.24 (VGS1), R54.2
unnamed: C68.1, C69.1, C70.1, IC2.7 (N/C), IC2.8 (VGS2), R55.2
unnamed: F2.1, J1.1
unnamed: F1.1, J1.3
unnamed: C10.1, J2.1 (In), R1.1
unnamed: C38.2, J4.1 (In)
unnamed: C59.1, J5.1 (In), JP7.2 (B), L11.2
unnamed: C98.2, J6.1 (In), L14.2
unnamed: C42.2, J7.1 (In), R24.1, R25.2
unnamed: JP1.1 (A), JP6.1 (A)
unnamed: HY1.6, JP1.3 (B), R28.1
unnamed: C38.1, JP1.2 (C)
unnamed: JP2.1 (A), JP4.1 (A)
unnamed: HY1.4, JP2.3 (B), R28.2
unnamed: HY1.2, JP4.3 (B)
unnamed: JP6.3 (B), L7.1
unnamed: C115.1, JP7.1 (A)
unnamed: JP8.1 (A), R23.2
unnamed: JP8.3 (B), Y1.4 (OUT)
unnamed: JP8.2 (C), R44.2, R45.1, U4.1, U4.3
unnamed: C43.1, JP9.1 (A)
unnamed: Q3.3 (D), R10.1
unnamed: Q3.1 (G), R7.1
unnamed: Q6.3 (D), R18.2, R20.1, R50.1
unnamed: Q6.1 (G), R48.1
unnamed: Q7.2 (B1), R4.2, R5.1
unnamed: Q7.6 (C1), R6.2, R7.2
unnamed: C5.1, Q7.5 (B2), R1.2, R2.1
unnamed: R13.2, RV1.3
unnamed: R18.1, RV3.1
unnamed: R20.2, RV4.3
unnamed: R39.1, RV2.3
unnamed: R40.2, RV2.1
unnamed: R52.2, RV3.3
unnamed: R53.2, RV4.1
unnamed: R54.1, RV4.2
unnamed: R55.1, RV3.2
unnamed: SW1.4, U1.5 (PA0)
unnamed: SW1.5, U1.6 (PA1)
unnamed: SW1.6, U1.7 (PA4)
unnamed: C9.2, R8.2, R9.1, U1.2 (PC14)
unnamed: D10.2 (DIN), R16.2, U1.3 (PC15)
unnamed: C65.1, R50.2, R51.1, U3.6 (PAEN)
unnamed: R42.2, R43.2, U3.2 (RFIN)
unnamed: R46.2, R47.1, U3.9 (RFOUT)
unnamed: C80.2, U5.4 (NR)
unnamed: C81.2, U6.4 (BP)
unnamed: C77.2, L21.2, U6.5 (VOUT)
unnamed: C84.2, U7.4 (BP)
unnamed: C78.2, L12.2, U8.5 (OUT)
unnamed: C104.2, U10.5 (FB1), U10.26 (BIAS)
unnamed: C102.1, U10.7 (BST1)
unnamed: C107.1, U10.15 (BST2)
unnamed: C111.1, R56.2, R57.1, U10.17 (FB2)
unnamed: C107.2, L19.1, U10.13 (LX2)
unnamed: C97.2, C113.2, L15.2, L17.1, U10.4 (OUT1)
unnamed: C109.2, C111.2, L19.2, L20.1, R56.1, U10.18 (OUT2)
unnamed: C106.2, C108.2, L18.1, U10.16 (SUPSW2)
unnamed: C47.2, RV2.2, Y1.1 (VC)
unnamed: C52.2, L6.2, R39.2, Y1.5 (VS)
VBUS: C4.2, C73.1, C75.2, C76.1, C82.1, C83.1, C85.1, C86.2, C99.2, C110.2, FL1.3, JP3.1 (A), JP5.2 (B), L16.1, L18.2; also elsewhere on the board

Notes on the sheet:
PLL + MIX
CONTROL
~4dBm clip.
36+13j -> 50 Z=35, L=2.5mm
PLL REF BUF
typ. 1dBm/0.7V pp max. 11dbm/2.3V pp
600MHz 50/75ohm -1dB @740MHz
REF ADJ
SWD ISP
125MHz 3rd ord. Cheb. 33/75ohm -42dB @740MHz
SRF=1G
LNB REF BUF
+37dBm max
SMPS
REF SEL
2.5V / RX 0.1V / TX
typ. 7dBm/1.4V pp max. 17dbm/4.5V pp
INV
PIN BIAS
REF ROUTE
±0.25ppm
-35..-42dB
REF TO LNB
PTT SENSE
TX ATT
BIAS SW
9.1V / RX 0.1V / TX
DRIVER
RX SPLIT
AUX SEL
IF SEL

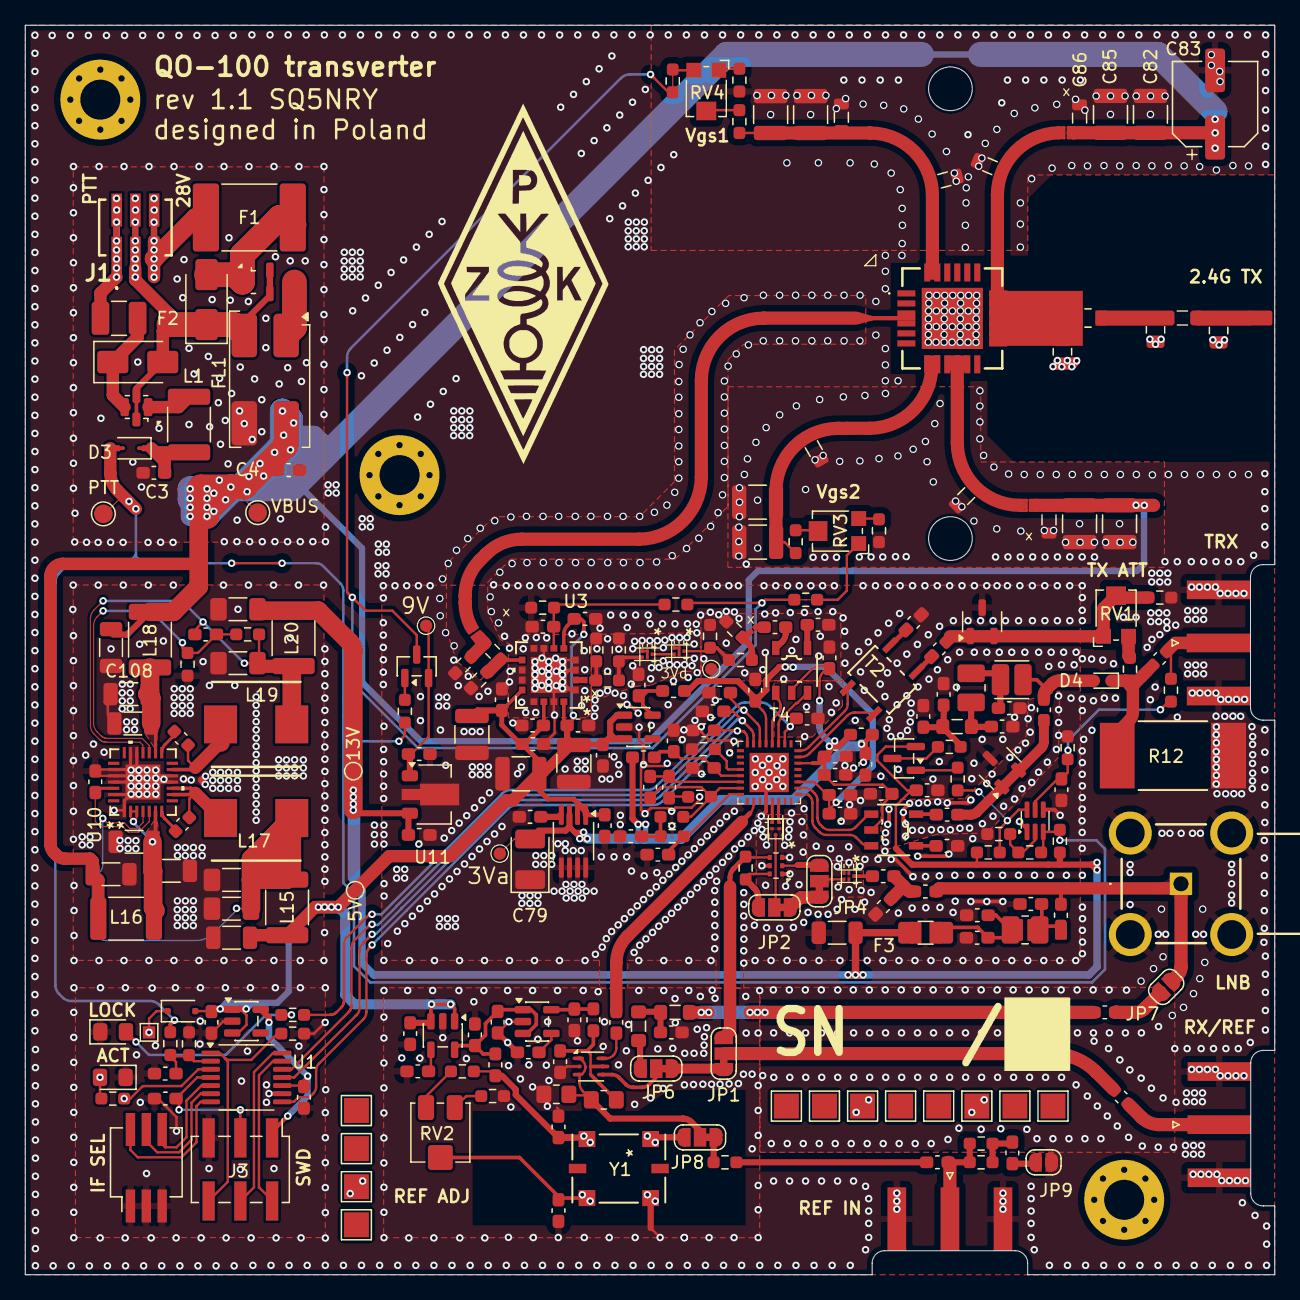
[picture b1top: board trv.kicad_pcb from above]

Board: 2 copper layers, 100.0 x 100.0 mm, 244 parts (0 on the bottom side), 141 nets.

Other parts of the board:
3Va, 3Vd, 9V: (no value)
5V, 13V: TestPoint_Pad_D1.0mm
PTT: PTT; TestPoint_Pad_D1.5mm
VBUS: 28V; TestPoint_Pad_D1.5mm

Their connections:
+3V0/A: 3Va.1; also elsewhere on the board
+3V0/D: 3Vd.1; also elsewhere on the board
+5V: 5V.1; also elsewhere on the board
+9V: 9V.1; also elsewhere on the board
+13V: 13V.1; also elsewhere on the board
//PA_ENABLE: PTT.1; also elsewhere on the board
VBUS: VBUS.1; also elsewhere on the board

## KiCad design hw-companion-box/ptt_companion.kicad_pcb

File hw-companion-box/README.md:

# Companion Box

Auxiliary unit for the QO-100 transverter, providing:

- 13.8V to 28V voltage boost for powering the transverter from a standard 13.8V shack supply
- PTT combiner: mixes PTT signal with RF on the coax line to the transverter

The built-in buzzer sounds an audible alert when the PTT line is unplugged — this is to notify the operator of a disconnected PTT cable before transmitting.

See [schematics](sch_companion_box.pdf) for details.

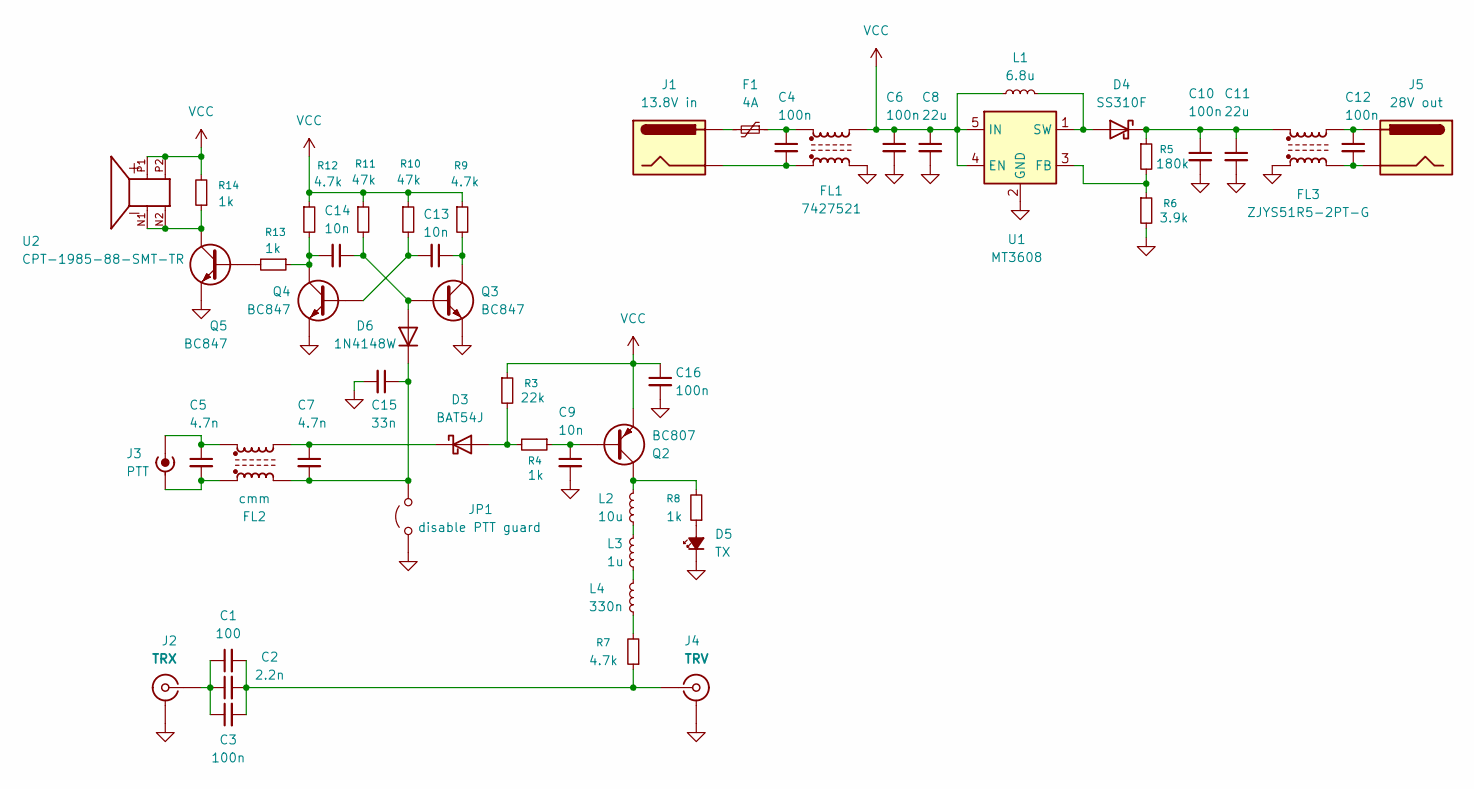
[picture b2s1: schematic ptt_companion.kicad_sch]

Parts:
C1: 100; C_0805_2012Metric_Pad1.18x1.45mm_HandSolder; Voltage 250V
C2: 2.2n; C_0805_2012Metric_Pad1.18x1.45mm_HandSolder; Voltage 250V
C3: 100n; C_0805_2012Metric_Pad1.18x1.45mm_HandSolder; Voltage 250V
C4, C6, C10, C12: 100n; C_0805_2012Metric_Pad1.18x1.45mm_HandSolder
C5, C7: 4.7n; C_0603_1608Metric_Pad1.08x0.95mm_HandSolder
C8, C11: 22u; C_1206_3216Metric_Pad1.33x1.80mm_HandSolder
C9, C13, C14: 10n; C_0603_1608Metric_Pad1.08x0.95mm_HandSolder
C15: 33n; C_0603_1608Metric_Pad1.08x0.95mm_HandSolder
C16: 100n; C_0603_1608Metric_Pad1.08x0.95mm_HandSolder
D3: BAT54J; D_SOD-323F
D4: SS310F; D_SMA_Handsoldering
D5: TX; LED_D5.0mm_Clear
D6: 1N4148W; D_SOD-123
F1: 4A; Fuse_2920_7451Metric_Pad2.10x5.45mm_HandSolder
FL1: 7427521; L_CommonMode_Delevan_4222
FL2: cmm; L_CommonMode_Wurth_WE-CNSW-1206
FL3: ZJYS51R5-2PT-G; L_CommonModeChoke_TDK_ACM7060
J1: 13.8V in; AMASS_XT30U-F_1x02_P5.0mm_Vertical
J2: TRX; MountingHole_5.3mm_M5_Pad_Via
J3: PTT; AMASS_XT30U-F_1x02_P5.0mm_Vertical
J4: TRV; MountingHole_5.3mm_M5_Pad_Via
J5: 28V out; AMASS_XT30U-F_1x02_P5.0mm_Vertical
JP1: disable PTT guard; SolderJumper-2_P1.3mm_Open_TrianglePad1.0x1.5mm
L1: 6.8u; L_Ferrocore_DLG-0403
L2: 10u; L_0805_2012Metric
L3: 1u; L_0805_2012Metric
L4: 330n; L_0805_2012Metric
Q2: BC807; SOT-23
Q3, Q4, Q5: BC847; SOT-23
R3: 22k; R_0603_1608Metric_Pad0.98x0.95mm_HandSolder
R4, R8, R13, R14: 1k; R_0603_1608Metric_Pad0.98x0.95mm_HandSolder
R5: 180k; R_0603_1608Metric_Pad0.98x0.95mm_HandSolder
R6: 3.9k; R_0603_1608Metric_Pad0.98x0.95mm_HandSolder
R7, R9, R12: 4.7k; R_0603_1608Metric_Pad0.98x0.95mm_HandSolder
R10, R11: 47k; R_0603_1608Metric_Pad0.98x0.95mm_HandSolder
U1: MT3608; SOT-23-6
U2: CPT-1985-88-SMT-TR; XDCR_CPT-1985-88-SMT-TR; PARTREV 1.0

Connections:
GND: C6.2, C8.2, C9.2, C10.2, C11.2, C15.2, C16.2, D5.1 (K), FL1.4, FL3.1, J2.2 (Ext), J4.2 (Ext), JP1.1 (A), Q3.2 (E), Q4.2 (E), Q5.2 (E), R6.2, U1.2 (GND)
unnamed: C4.1, F1.1, FL1.1
unnamed: C4.2, FL1.3, J1.2
unnamed: C12.1, FL3.4, J5.1
unnamed: C12.2, FL3.2, J5.2
unnamed: D3.2 (A), R3.2, R4.2
unnamed: C7.1, D3.1 (K), FL2.4
unnamed: D4.2 (A), L1.1, U1.1 (SW)
unnamed: C10.1, C11.1, D4.1 (K), FL3.3, R5.1
unnamed: D5.2 (A), R8.1
unnamed: C14.1, D6.2 (A), Q3.1 (B), R11.2
unnamed: C7.2, C15.1, D6.1 (K), FL2.2, JP1.2 (B)
unnamed: F1.2, J1.1
unnamed: C1.1, C2.1, C3.1, J2.1 (In)
unnamed: C5.2, FL2.1, J3.2 (Ext)
unnamed: C5.1, FL2.3, J3.1 (In)
unnamed: C1.2, C2.2, C3.2, J4.1 (In), R7.1
unnamed: L2.1, L3.2
unnamed: L3.1, L4.2
unnamed: L4.1, R7.2
unnamed: C9.1, Q2.1 (B), R4.1
unnamed: L2.2, Q2.3 (C), R8.2
unnamed: C13.1, Q3.3 (C), R9.2
unnamed: C13.2, Q4.1 (B), R10.2
unnamed: C14.2, Q4.3 (C), R12.2, R13.1
unnamed: Q5.1 (B), R13.2
unnamed: Q5.3 (C), R14.1, U2.N1, U2.N2
unnamed: R5.2, R6.1, U1.3 (FB)
VCC: C6.1, C8.1, C16.1, FL1.2, L1.2, Q2.2 (E), R3.1, R9.1, R10.1, R11.1, R12.1, R14.2, U1.4 (EN), U1.5 (IN), U2.P1, U2.P2

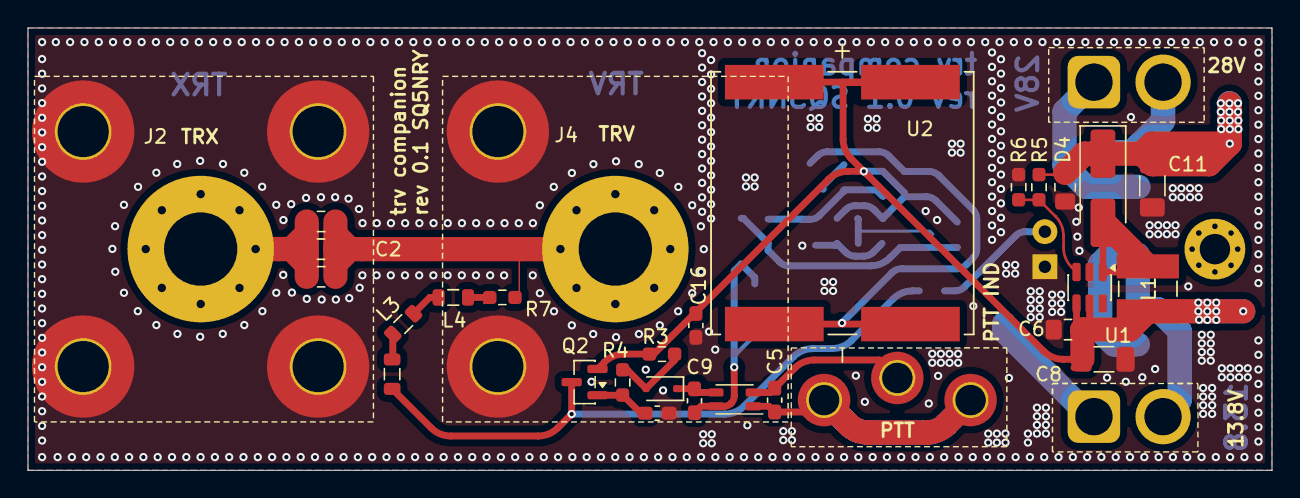
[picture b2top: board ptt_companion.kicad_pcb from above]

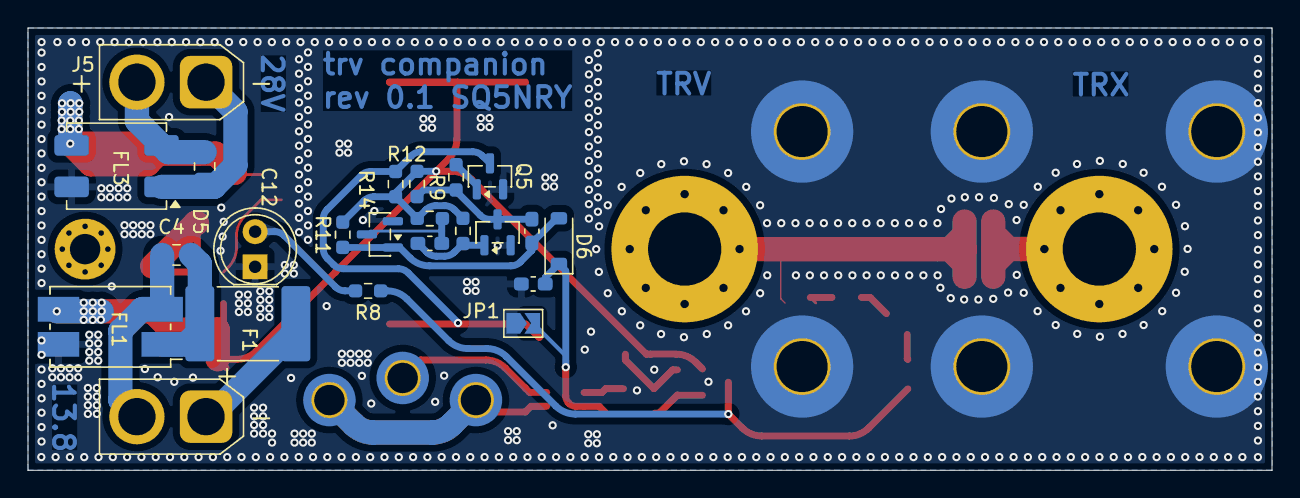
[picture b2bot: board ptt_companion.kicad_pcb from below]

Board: 2 copper layers, 90.0 x 32.0 mm, 51 parts (23 on the bottom side), 29 nets.

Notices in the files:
README.md:
License:
All source code, hardware design files, and documentation are publicly available — schematics, PCB layout, and firmware can be freely studied, built, and modified for personal and amateur radio use. This project is dual-licensed by component, and **commercial use of any part of it is not permitted**:
Component | License
Firmware (`src/`, excluding bundled vendor drivers) | [GPL v2 + commercial exception](LICENSE-CODE)
Hardware design (`hw-trv/`, `hw-companion-box/`), manual, docs/media | [CC BY-NC-SA 4.0](LICENSE-HARDWARE)
See [LICENSE](LICENSE) for the full overview.
